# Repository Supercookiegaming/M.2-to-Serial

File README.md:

# M.2-to-Serial

## Overview
The goals of this project is to utilize the UART lines on E key M.2 conbnectors to make serial ports. There are plans to have multiple types of serial ports. Currently the [RPI UART standard](https://datasheets.raspberrypi.com/debug/debug-connector-specification.pdf) has been mostly implemented and an RS-232 header is currently being developed. If you have a specific connector you want please make a feature request in the issues section.

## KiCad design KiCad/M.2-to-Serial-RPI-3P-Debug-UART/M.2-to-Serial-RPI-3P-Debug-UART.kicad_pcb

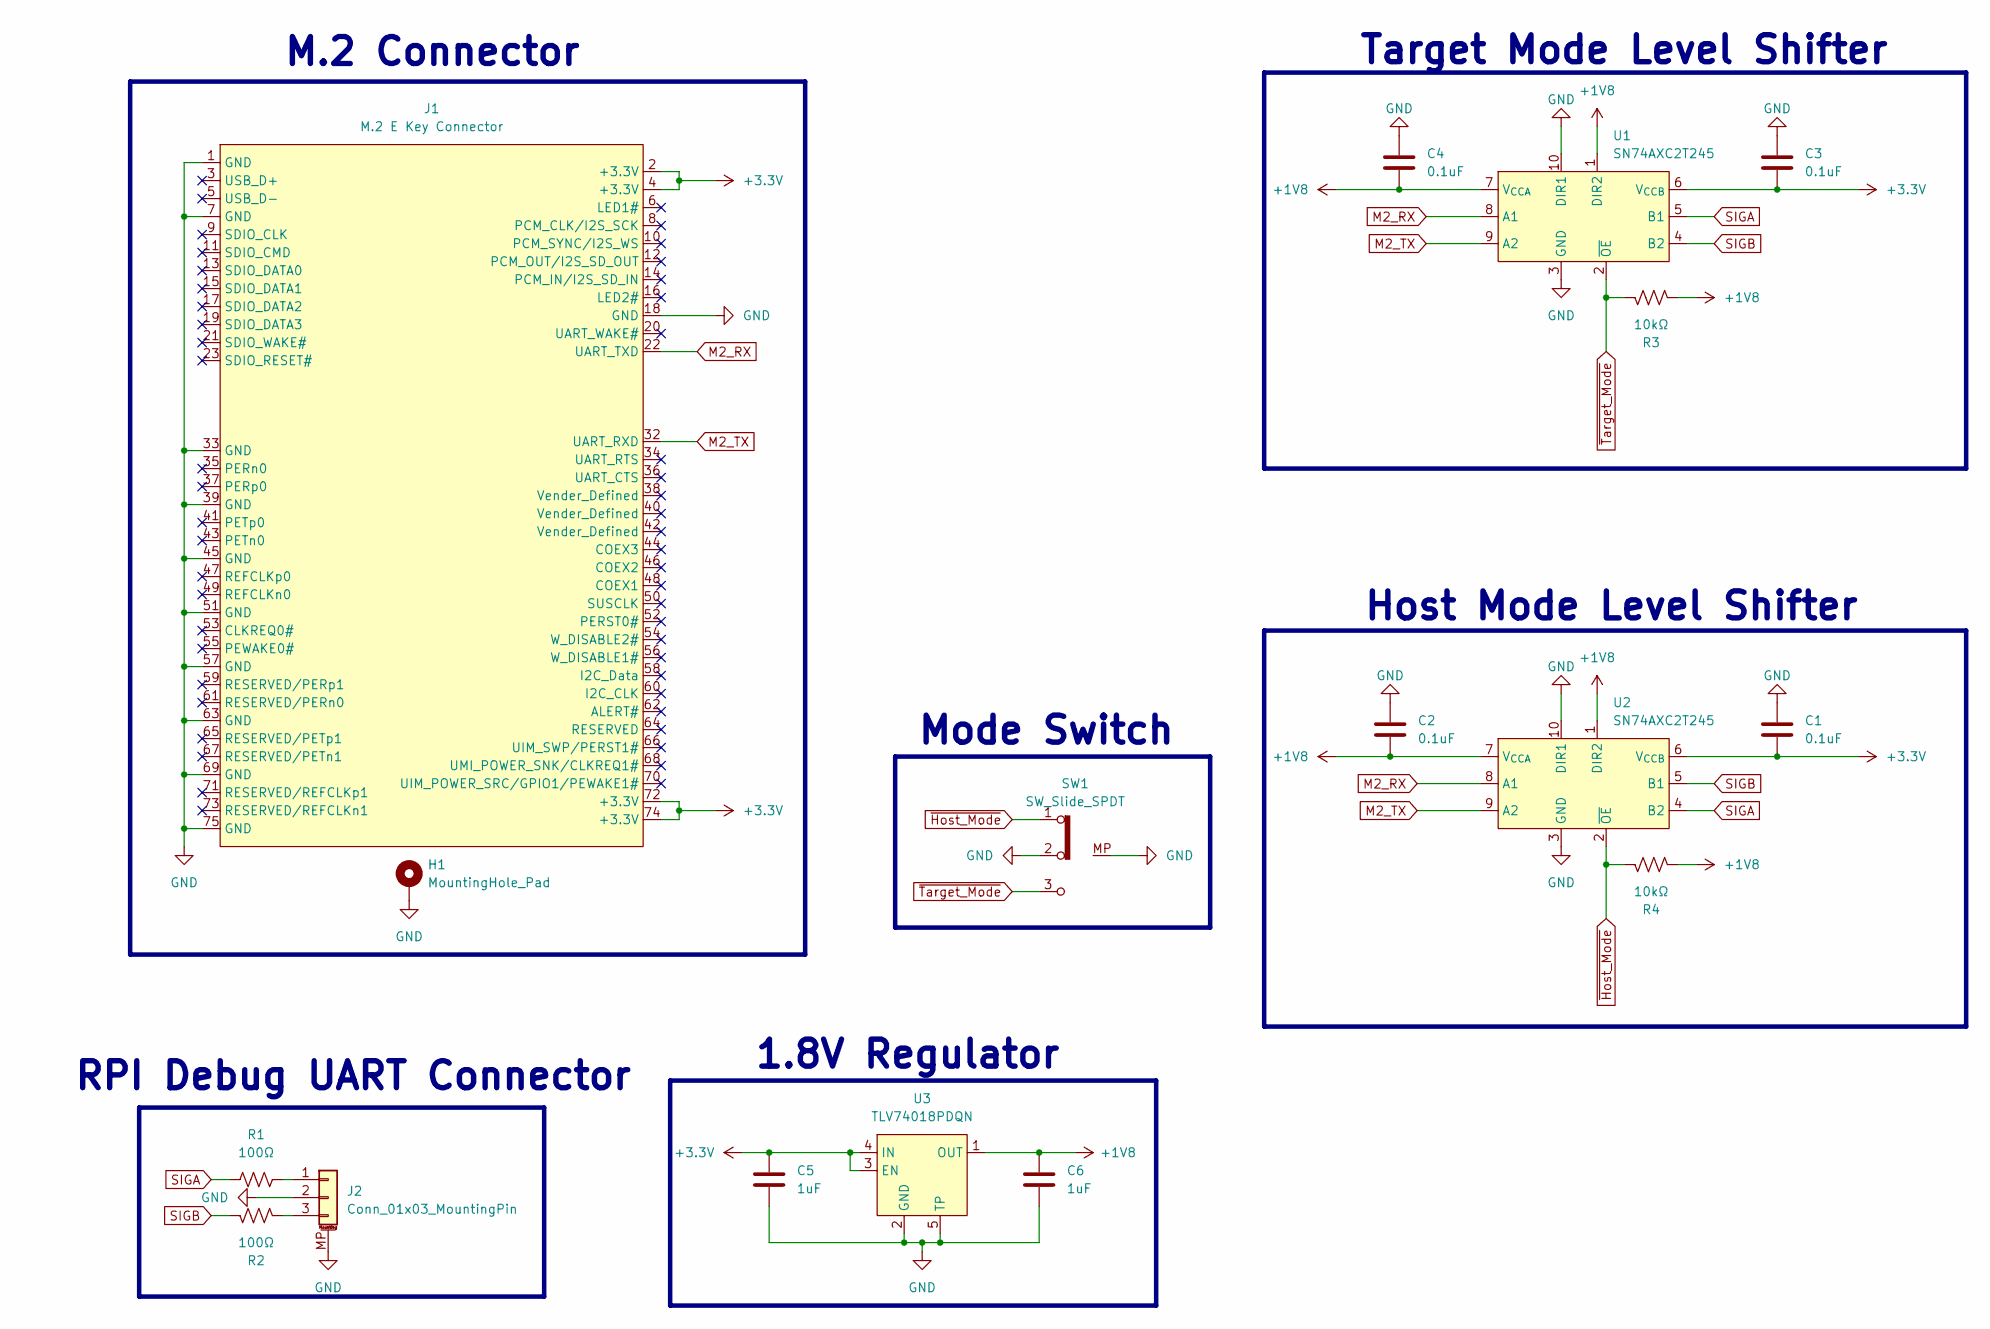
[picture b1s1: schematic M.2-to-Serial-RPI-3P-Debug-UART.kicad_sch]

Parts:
C1, C2, C3, C4: 0.1uF; C_0402_1005Metric
C5, C6: 1uF; C_0402_1005Metric
H1: MountingHole_Pad; M.2 Mounting Pad
J1: M.2 E Key Connector
J2: Conn_01x03_MountingPin; JST_SH_SM03B-SRSS-TB_1x03-1MP_P1.00mm_Horizontal
R1, R2: 100Ω; R_0402_1005Metric
R3, R4: 10kΩ; R_0402_1005Metric
SW1: SW_Slide_SPDT; SLW-66527511-SMT-TR
U1, U2: SN74AXC2T245
U3: TLV74018PDQN

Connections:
+1V8: C2.2, C4.2, C6.1, R3.1, R4.1, U1.1 (DIR2), U1.7 (V_{CCA}), U2.1 (DIR2), U2.7 (V_{CCA}), U3.1 (OUT)
+3.3V: C1.2, C3.2, C5.1, J1.2 (+3.3V), J1.4 (+3.3V), J1.72 (+3.3V), J1.74 (+3.3V), U1.6 (V_{CCB}), U2.6 (V_{CCB}), U3.3 (EN), U3.4 (IN)
GND: C1.1, C2.1, C3.1, C4.1, C5.2, C6.2, H1.1, J1.1 (GND), J1.7 (GND), J1.18 (GND), J1.33 (GND), J1.39 (GND), J1.45 (GND), J1.51 (GND), J1.57 (GND), J1.63 (GND), J1.69 (GND), J1.75 (GND), J2.2, J2.MP (MountPin), SW1.2 (B), SW1.MP, U1.3 (GND), U1.10 (DIR1), U2.3 (GND), U2.10 (DIR1), U3.2 (GND), U3.5 (TP)
M2_RX: J1.22 (UART_TXD), U1.8 (A1), U2.8 (A1)
M2_TX: J1.32 (UART_RXD), U1.9 (A2), U2.9 (A2)
unnamed: J2.1, R1.2
unnamed: J2.3, R2.1
SIGA: R1.1, U1.5 (B1), U2.4 (B2)
SIGB: R2.2, U1.4 (B2), U2.5 (B1)
~Host_Mode: R4.2, SW1.1 (A), U2.2 (~OE)
~Target_Mode: R3.2, SW1.3 (C), U1.2 (~OE)

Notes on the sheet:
Target Mode Level Shifter
M.2 Connector
1.8V Regulator
Mode Switch
Host Mode Level Shifter
RPI Debug UART Connector

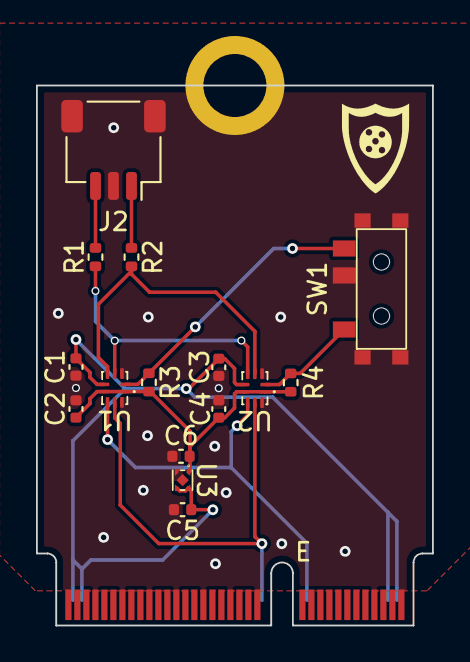
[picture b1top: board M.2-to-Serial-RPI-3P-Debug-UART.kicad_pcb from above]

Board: 2 copper layers, 22.0 x 30.0 mm, 17 parts (0 on the bottom side), 11 nets.

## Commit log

2025-08-16 added rpi 3p debug uart version
    -added rpi 3 pin debug uart standard version of converter
    -added schematic, kicad, gerber, 3d render, bom
    -added project library files
    -started work on rs232 AT/EVEREX version of converter
